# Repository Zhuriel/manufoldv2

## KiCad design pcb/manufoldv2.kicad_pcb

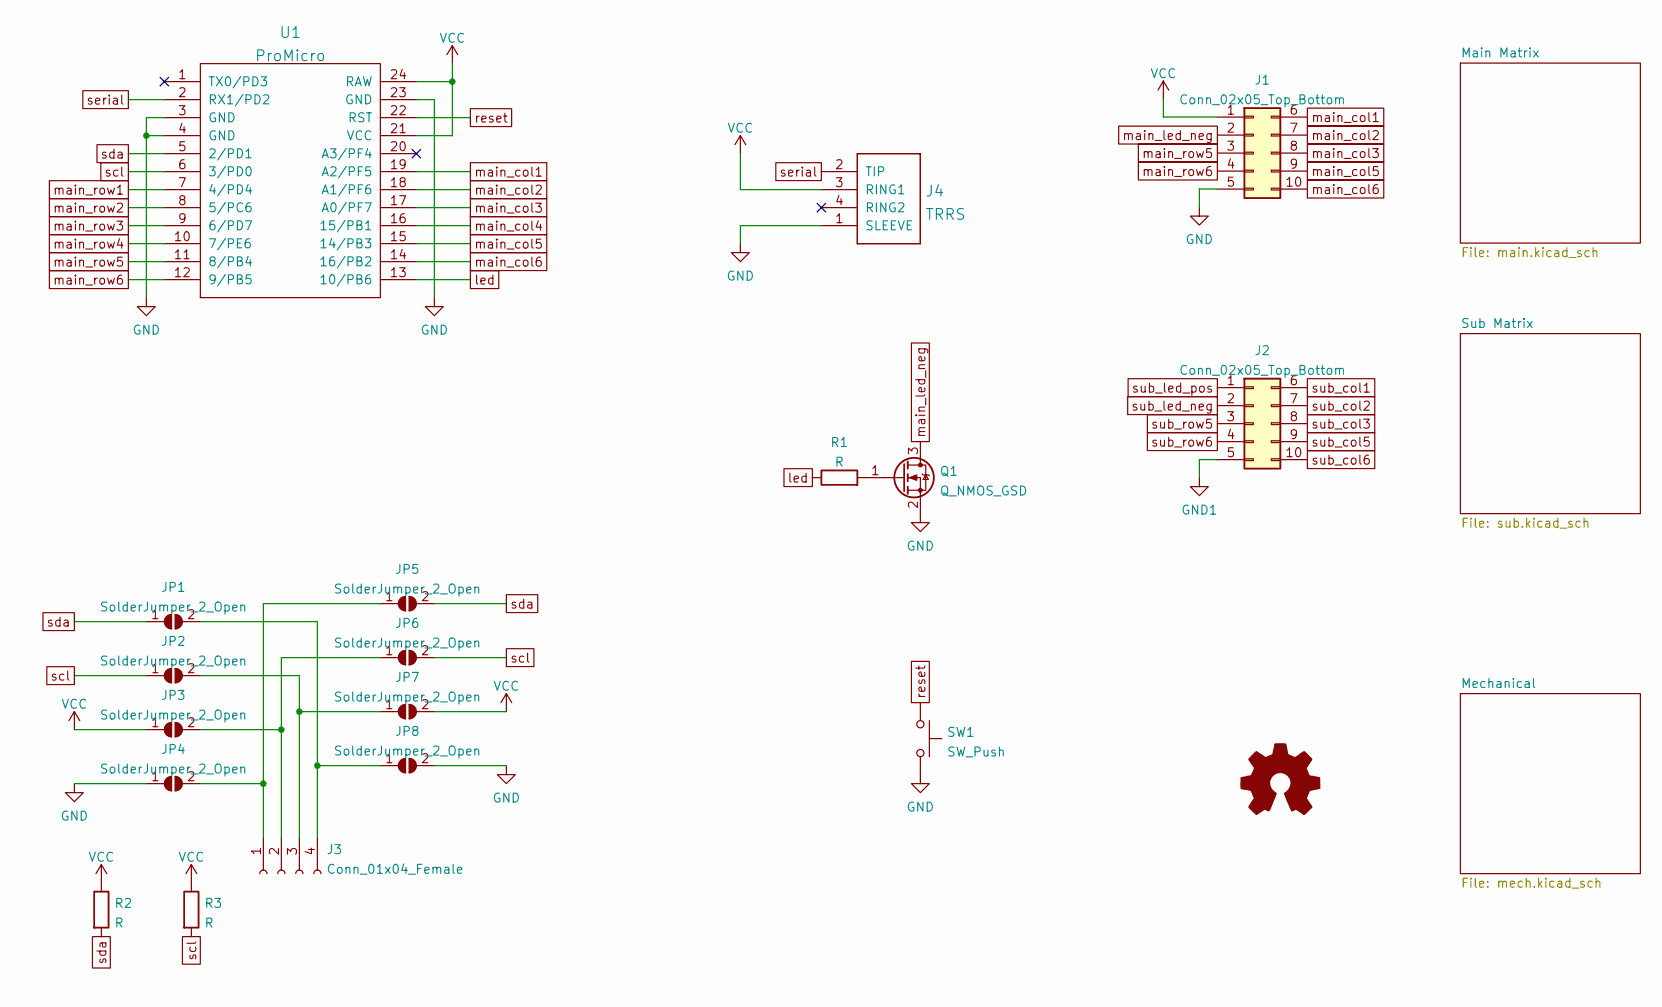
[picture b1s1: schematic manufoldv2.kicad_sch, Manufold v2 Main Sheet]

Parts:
J1: Conn_02x05_Top_Bottom; PinHeader_2x05_P1.27mm_Horizontal
J2: Conn_02x05_Top_Bottom; PinSocket_2x05_P1.27mm_Vertical
J3: Conn_01x04_Female; PinSocket_1x04_P2.54mm_Vertical
J4: TRRS; TRRS-PJ-320A-dual
JP1, JP2, JP3, JP4, JP5, JP6, JP7, JP8: SolderJumper_2_Open; SolderJumper-2_P1.3mm_Open_RoundedPad1.0x1.5mm
Q1: Q_NMOS_GSD; SOT-23_Handsoldering
R1, R2, R3: R; R_0805_2012Metric
SW1: SW_Push; SolderJumper-2_P1.3mm_Open_RoundedPad1.0x1.5mm
U1: ProMicro; promicro_dual

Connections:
GND: J1.5, J4.1 (SLEEVE), JP4.1 (A), JP8.2 (B), Q1.2 (S), SW1.2, U1.3 (GND), U1.4 (GND), U1.23 (GND); also elsewhere on the board
GND1: J2.5; also elsewhere on the board
unnamed: J3.1, JP4.2 (B), JP5.1 (A)
unnamed: J3.2, JP3.2 (B), JP6.1 (A)
unnamed: J3.3, JP2.2 (B), JP7.1 (A)
unnamed: J3.4, JP1.2 (B), JP8.1 (A)
unnamed: Q1.1 (G), R1.2
VCC: J1.1, J4.3 (RING1), JP3.1 (A), JP7.2 (B), R2.1, R3.1, U1.21 (VCC), U1.24 (RAW); also elsewhere on the board
led: R1.1, U1.13 (10/PB6)
main_col1: J1.6, U1.19 (A2/PF5); also elsewhere on the board
main_col2: J1.7, U1.18 (A1/PF6); also elsewhere on the board
main_col3: J1.8, U1.17 (A0/PF7); also elsewhere on the board
main_col4: U1.16 (15/PB1); also elsewhere on the board
main_col5: J1.9, U1.15 (14/PB3); also elsewhere on the board
main_col6: J1.10, U1.14 (16/PB2); also elsewhere on the board
main_led_neg: J1.2, Q1.3 (D); also elsewhere on the board
main_row1: U1.7 (4/PD4); also elsewhere on the board
main_row2: U1.8 (5/PC6); also elsewhere on the board
main_row3: U1.9 (6/PD7); also elsewhere on the board
main_row4: U1.10 (7/PE6); also elsewhere on the board
main_row5: J1.3, U1.11 (8/PB4); also elsewhere on the board
main_row6: J1.4, U1.12 (9/PB5)
reset: SW1.1, U1.22 (RST)
scl: JP2.1 (A), JP6.2 (B), R3.2, U1.6 (3/PD0)
sda: JP1.1 (A), JP5.2 (B), R2.2, U1.5 (2/PD1)
serial: J4.2 (TIP), U1.2 (RX1/PD2)
sub_col1: J2.6; also elsewhere on the board
sub_col2: J2.7; also elsewhere on the board
sub_col3: J2.8; also elsewhere on the board
sub_col5: J2.9; also elsewhere on the board
sub_col6: J2.10; also elsewhere on the board
sub_led_neg: J2.2; also elsewhere on the board
sub_led_pos: J2.1; also elsewhere on the board
sub_row5: J2.3; also elsewhere on the board
sub_row6: J2.4; also elsewhere on the board

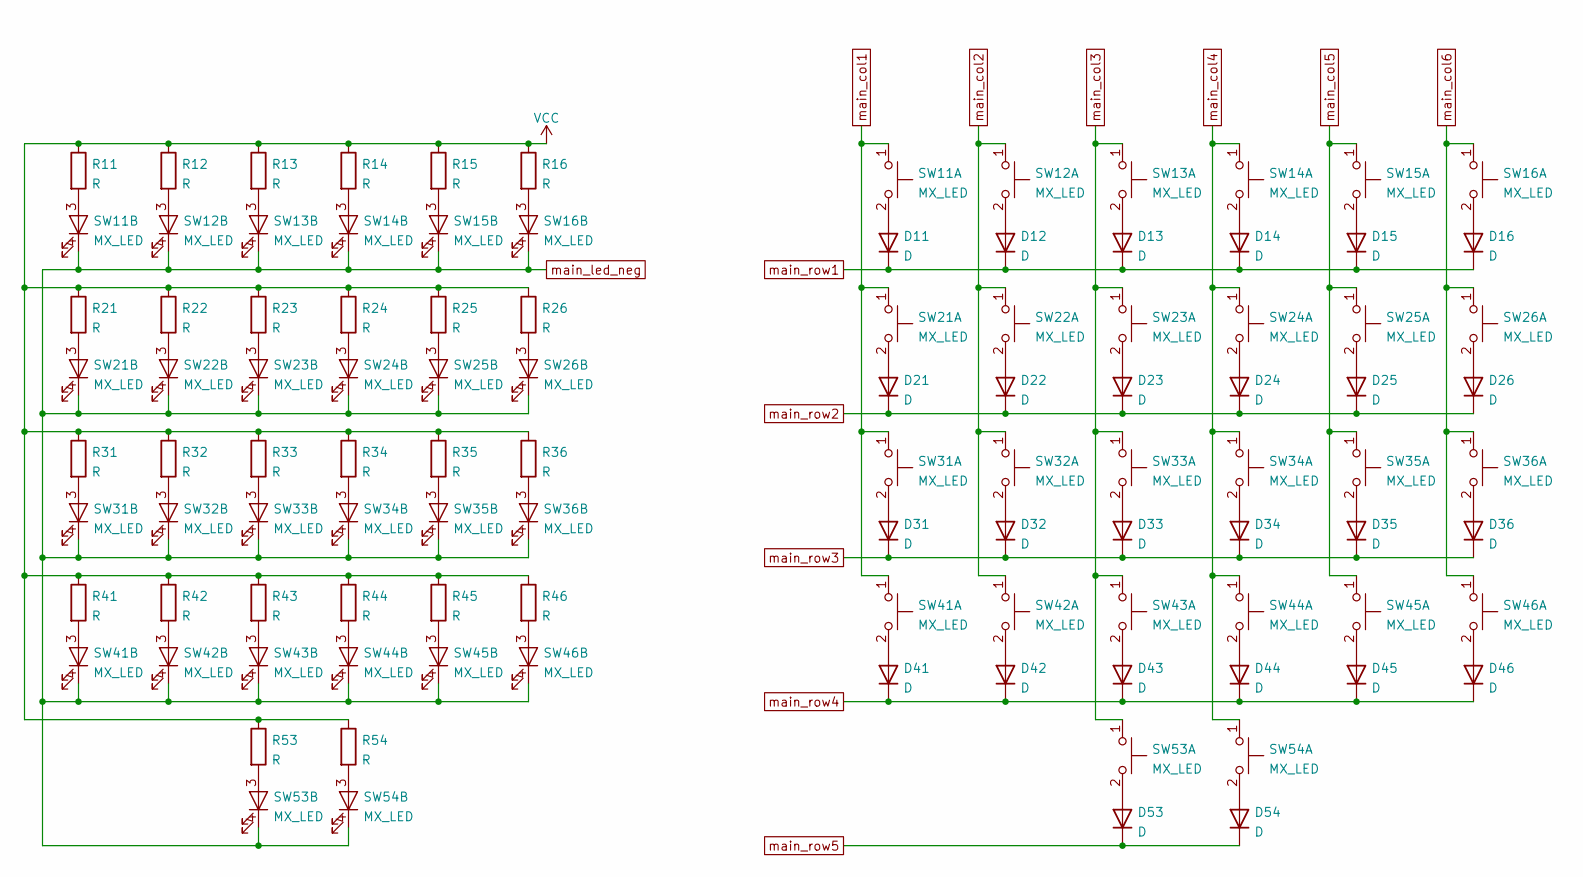
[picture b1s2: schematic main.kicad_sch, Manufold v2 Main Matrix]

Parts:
D11, D12, D13, D14, D15, D16, D21, D22, D23, D24, D25, D26, D31, D32, D33, D34, D35, D36, D41, D42, D43, D44, D45, D46, D53, D54: D; Diode-dual
R11, R12, R13, R14, R15, R16, R21, R22, R23, R24, R25, R26, R31, R32, R33, R34, R35, R36, R41, R42, R43, R44, R45, R46, R53, R54: R; Resistor-Hybrid
SW11, SW12, SW13, SW14, SW15, SW16, SW21, SW22, SW23, SW24, SW25, SW26, SW31, SW32, SW33, SW34, SW35, SW36, SW41, SW42, SW43, SW44, SW45, SW46, SW53, SW54: MX_LED; Triple-Dual-1u-LED

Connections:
unnamed: D11.2 (A), SW11.2
unnamed: D12.2 (A), SW12.2
unnamed: D13.2 (A), SW13.2
unnamed: D14.2 (A), SW14.2
unnamed: D15.2 (A), SW15.2
unnamed: D16.2 (A), SW16.2
unnamed: D21.2 (A), SW21.2
unnamed: D22.2 (A), SW22.2
unnamed: D23.2 (A), SW23.2
unnamed: D24.2 (A), SW24.2
unnamed: D25.2 (A), SW25.2
unnamed: D26.2 (A), SW26.2
unnamed: D31.2 (A), SW31.2
unnamed: D32.2 (A), SW32.2
unnamed: D33.2 (A), SW33.2
unnamed: D34.2 (A), SW34.2
unnamed: D35.2 (A), SW35.2
unnamed: D36.2 (A), SW36.2
unnamed: D41.2 (A), SW41.2
unnamed: D42.2 (A), SW42.2
unnamed: D43.2 (A), SW43.2
unnamed: D44.2 (A), SW44.2
unnamed: D45.2 (A), SW45.2
unnamed: D46.2 (A), SW46.2
unnamed: D53.2 (A), SW53.2
unnamed: D54.2 (A), SW54.2
unnamed: R11.2, SW11.3
unnamed: R12.2, SW12.3
unnamed: R13.2, SW13.3
unnamed: R14.2, SW14.3
unnamed: R15.2, SW15.3
unnamed: R16.2, SW16.3
unnamed: R21.2, SW21.3
unnamed: R22.2, SW22.3
unnamed: R23.2, SW23.3
unnamed: R24.2, SW24.3
unnamed: R25.2, SW25.3
unnamed: R26.2, SW26.3
unnamed: R31.2, SW31.3
unnamed: R32.2, SW32.3
unnamed: R33.2, SW33.3
unnamed: R34.2, SW34.3
unnamed: R35.2, SW35.3
unnamed: R36.2, SW36.3
unnamed: R41.2, SW41.3
unnamed: R42.2, SW42.3
unnamed: R43.2, SW43.3
unnamed: R44.2, SW44.3
unnamed: R45.2, SW45.3
unnamed: R46.2, SW46.3
unnamed: R53.2, SW53.3
unnamed: R54.2, SW54.3
VCC: R11.1, R12.1, R13.1, R14.1, R15.1, R16.1, R21.1, R22.1, R23.1, R24.1, R25.1, R26.1, R31.1, R32.1, R33.1, R34.1, R35.1, R36.1, R41.1, R42.1, R43.1, R44.1, R45.1, R46.1, R53.1, R54.1; also elsewhere on the board
main_col1: SW11.1, SW21.1, SW31.1, SW41.1; also elsewhere on the board
main_col2: SW12.1, SW22.1, SW32.1, SW42.1; also elsewhere on the board
main_col3: SW13.1, SW23.1, SW33.1, SW43.1, SW53.1; also elsewhere on the board
main_col4: SW14.1, SW24.1, SW34.1, SW44.1, SW54.1; also elsewhere on the board
main_col5: SW15.1, SW25.1, SW35.1, SW45.1; also elsewhere on the board
main_col6: SW16.1, SW26.1, SW36.1, SW46.1; also elsewhere on the board
main_led_neg: SW11.4, SW12.4, SW13.4, SW14.4, SW15.4, SW16.4, SW21.4, SW22.4, SW23.4, SW24.4, SW25.4, SW26.4, SW31.4, SW32.4, SW33.4, SW34.4, SW35.4, SW36.4, SW41.4, SW42.4, SW43.4, SW44.4, SW45.4, SW46.4, SW53.4, SW54.4; also elsewhere on the board
main_row1: D11.1 (K), D12.1 (K), D13.1 (K), D14.1 (K), D15.1 (K), D16.1 (K); also elsewhere on the board
main_row2: D21.1 (K), D22.1 (K), D23.1 (K), D24.1 (K), D25.1 (K), D26.1 (K); also elsewhere on the board
main_row3: D31.1 (K), D32.1 (K), D33.1 (K), D34.1 (K), D35.1 (K), D36.1 (K); also elsewhere on the board
main_row4: D41.1 (K), D42.1 (K), D43.1 (K), D44.1 (K), D45.1 (K), D46.1 (K); also elsewhere on the board
main_row5: D53.1 (K), D54.1 (K); also elsewhere on the board

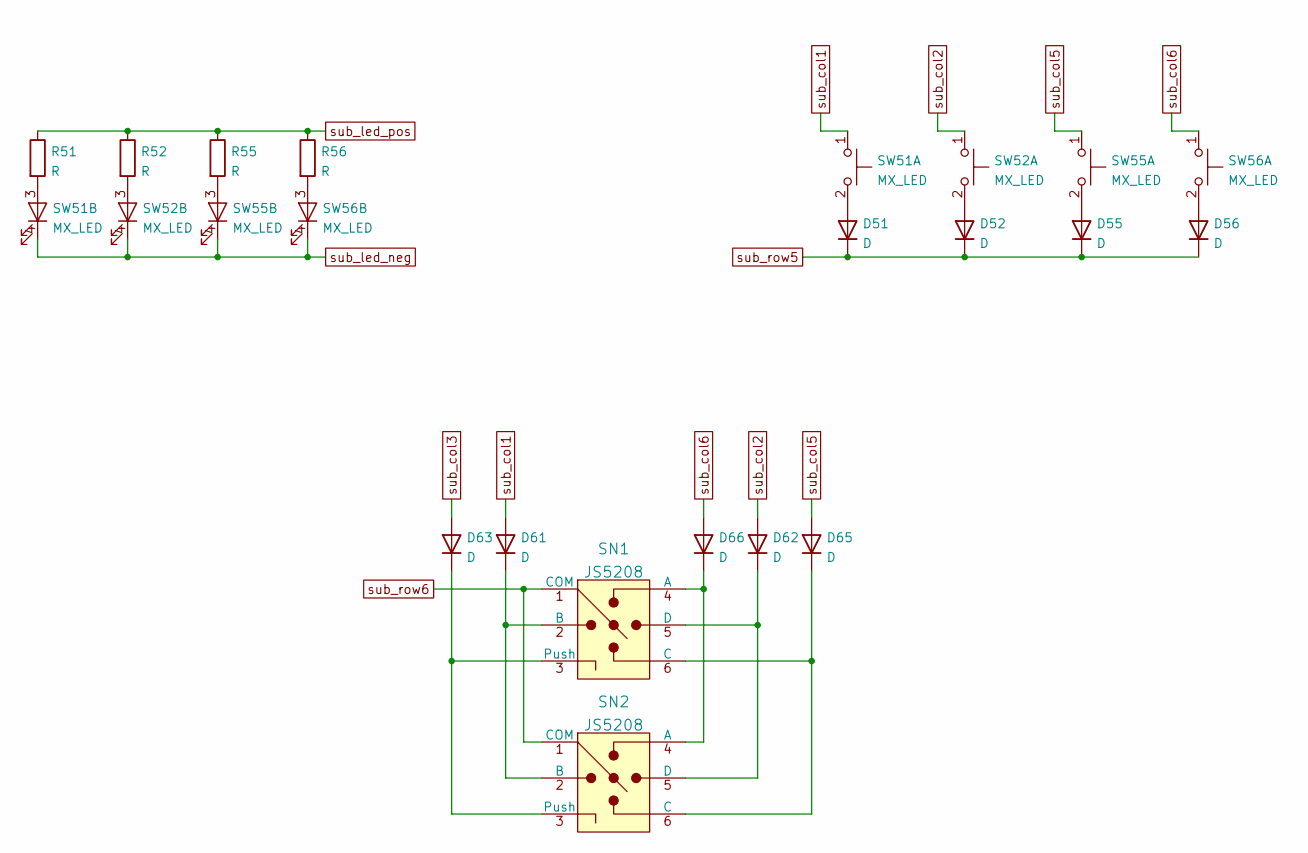
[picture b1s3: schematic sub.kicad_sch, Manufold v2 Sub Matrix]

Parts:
D51, D52, D55, D56: D; Diode-dual
D61, D62, D63, D65, D66: D; D_SOD123F
R51, R52, R55, R56: R; Resistor-Hybrid
SN1, SN2: JS5208; Switch_Nav_12.4x12.4mm_SMD_JS5208; MPN JS5208; Digi-Key_PN EG4561-ND
SW51, SW52, SW55, SW56: MX_LED; Triple-Dual-1u-LED

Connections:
unnamed: D51.2 (A), SW51.2
unnamed: D52.2 (A), SW52.2
unnamed: D55.2 (A), SW55.2
unnamed: D56.2 (A), SW56.2
unnamed: D61.1 (K), SN1.2 (B), SN2.2 (B)
unnamed: D62.1 (K), SN1.5 (D), SN2.5 (D)
unnamed: D63.1 (K), SN1.3 (Push), SN2.3 (Push)
unnamed: D65.1 (K), SN1.6 (C), SN2.6 (C)
unnamed: D66.1 (K), SN1.4 (A), SN2.4 (A)
unnamed: R51.2, SW51.3
unnamed: R52.2, SW52.3
unnamed: R55.2, SW55.3
unnamed: R56.2, SW56.3
sub_col1: D61.2 (A), SW51.1; also elsewhere on the board
sub_col2: D62.2 (A), SW52.1; also elsewhere on the board
sub_col3: D63.2 (A); also elsewhere on the board
sub_col5: D65.2 (A), SW55.1; also elsewhere on the board
sub_col6: D66.2 (A), SW56.1; also elsewhere on the board
sub_led_neg: SW51.4, SW52.4, SW55.4, SW56.4; also elsewhere on the board
sub_led_pos: R51.1, R52.1, R55.1, R56.1; also elsewhere on the board
sub_row5: D51.1 (K), D52.1 (K), D55.1 (K), D56.1 (K); also elsewhere on the board
sub_row6: SN1.1 (COM), SN2.1 (COM); also elsewhere on the board

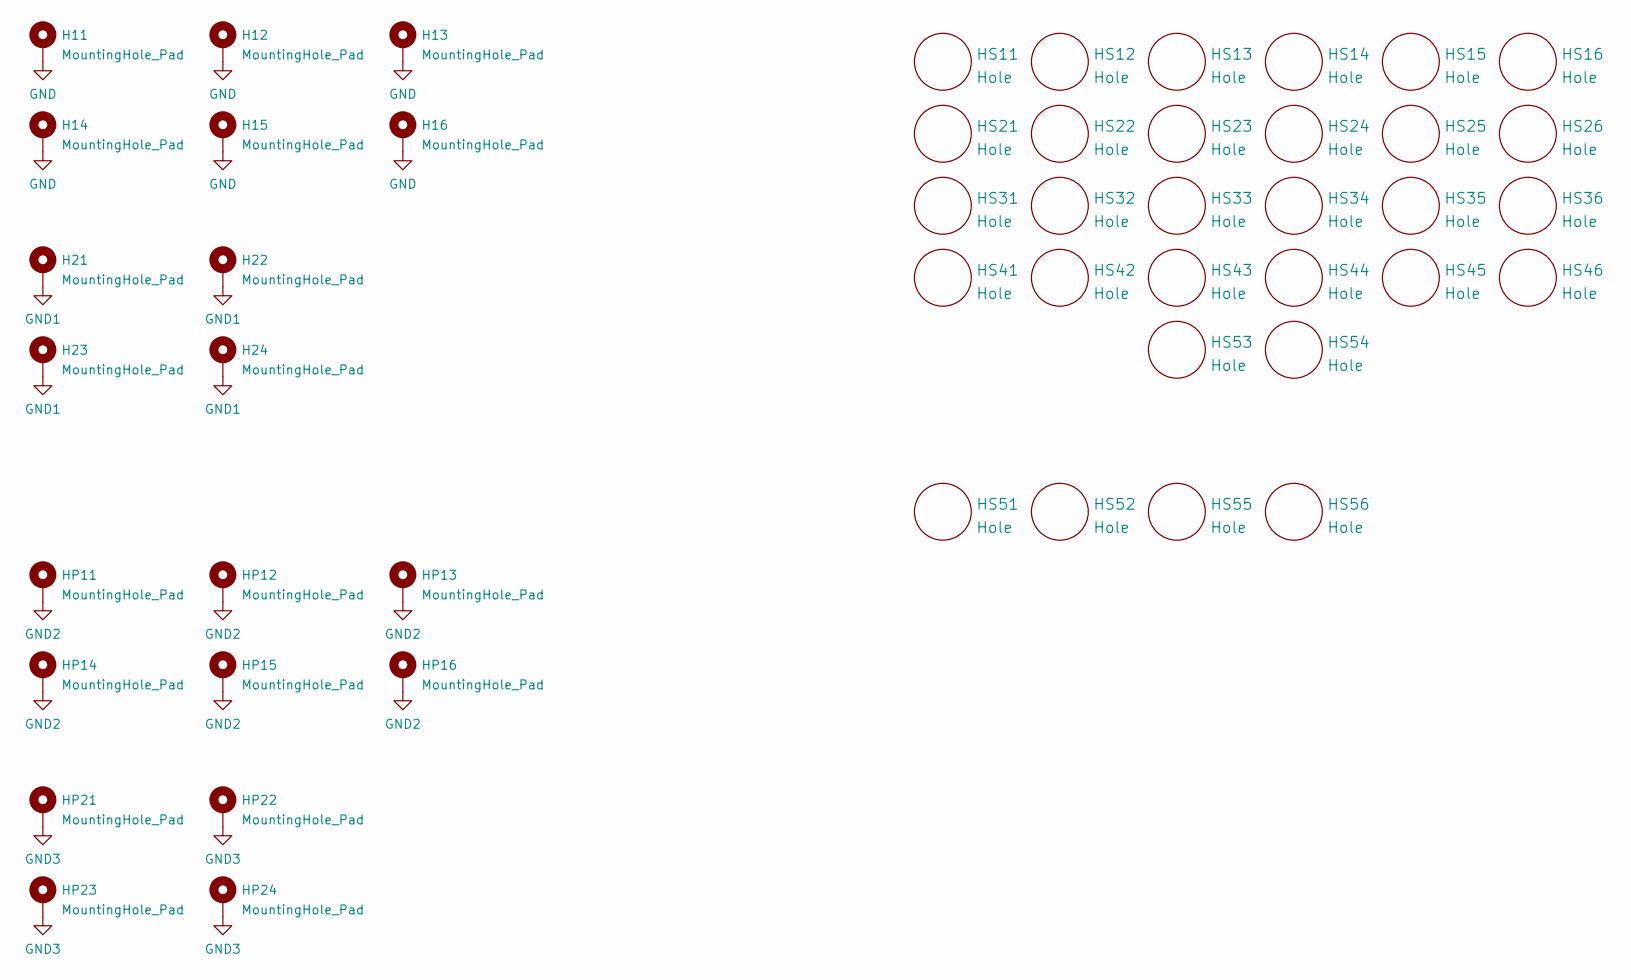
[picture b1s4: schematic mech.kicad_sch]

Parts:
H11, H12, H13, H14, H15, H16, H21, H22, H23, H24: MountingHole_Pad; MountingHole_2.2mm_M2_DIN965_Pad
HP11, HP12, HP13, HP14, HP15, HP16, HP21, HP22, HP23, HP24: MountingHole_Pad; MountingHole_2.2mm_M2_DIN965_Pad
HS11, HS12, HS13, HS14, HS15, HS16, HS21, HS22, HS23, HS24, HS25, HS26, HS31, HS32, HS33, HS34, HS35, HS36, HS41, HS42, HS43, HS44, HS45, HS46, HS51, HS52, HS53, HS54, HS55, HS56: Hole; MX_Switch_Cutout

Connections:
GND: H11.1, H12.1, H13.1, H14.1, H15.1, H16.1; also elsewhere on the board
GND1: H21.1, H22.1, H23.1, H24.1; also elsewhere on the board
GND2: HP11.1, HP12.1, HP13.1, HP14.1, HP15.1, HP16.1
GND3: HP21.1, HP22.1, HP23.1, HP24.1

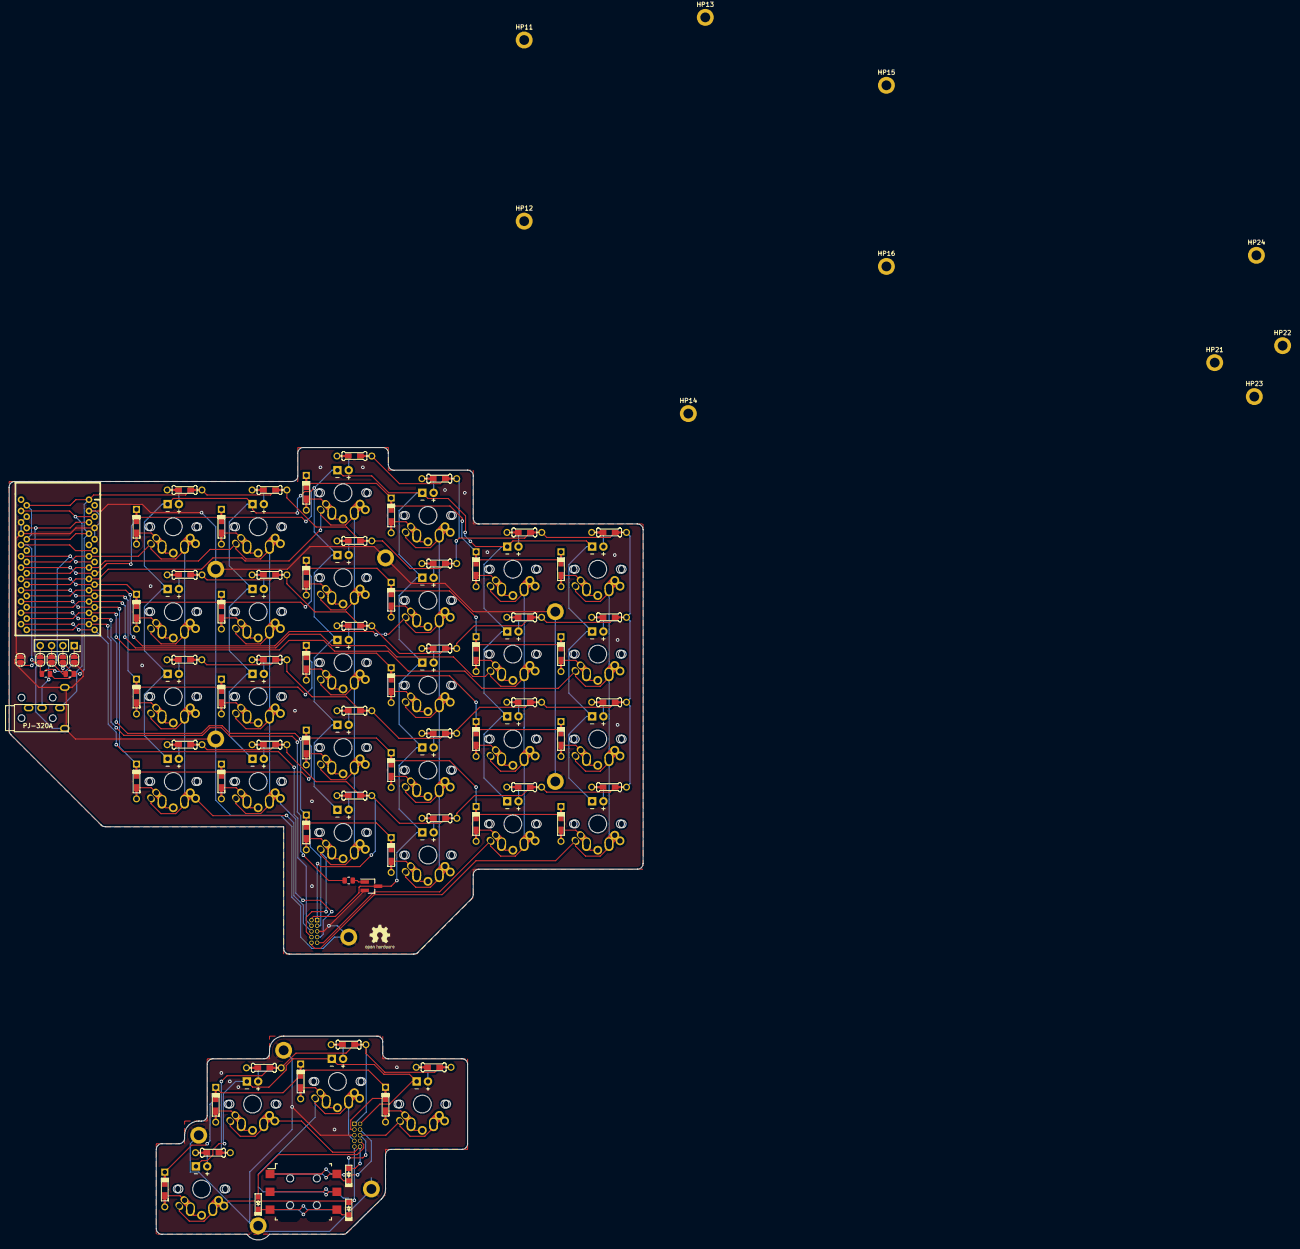
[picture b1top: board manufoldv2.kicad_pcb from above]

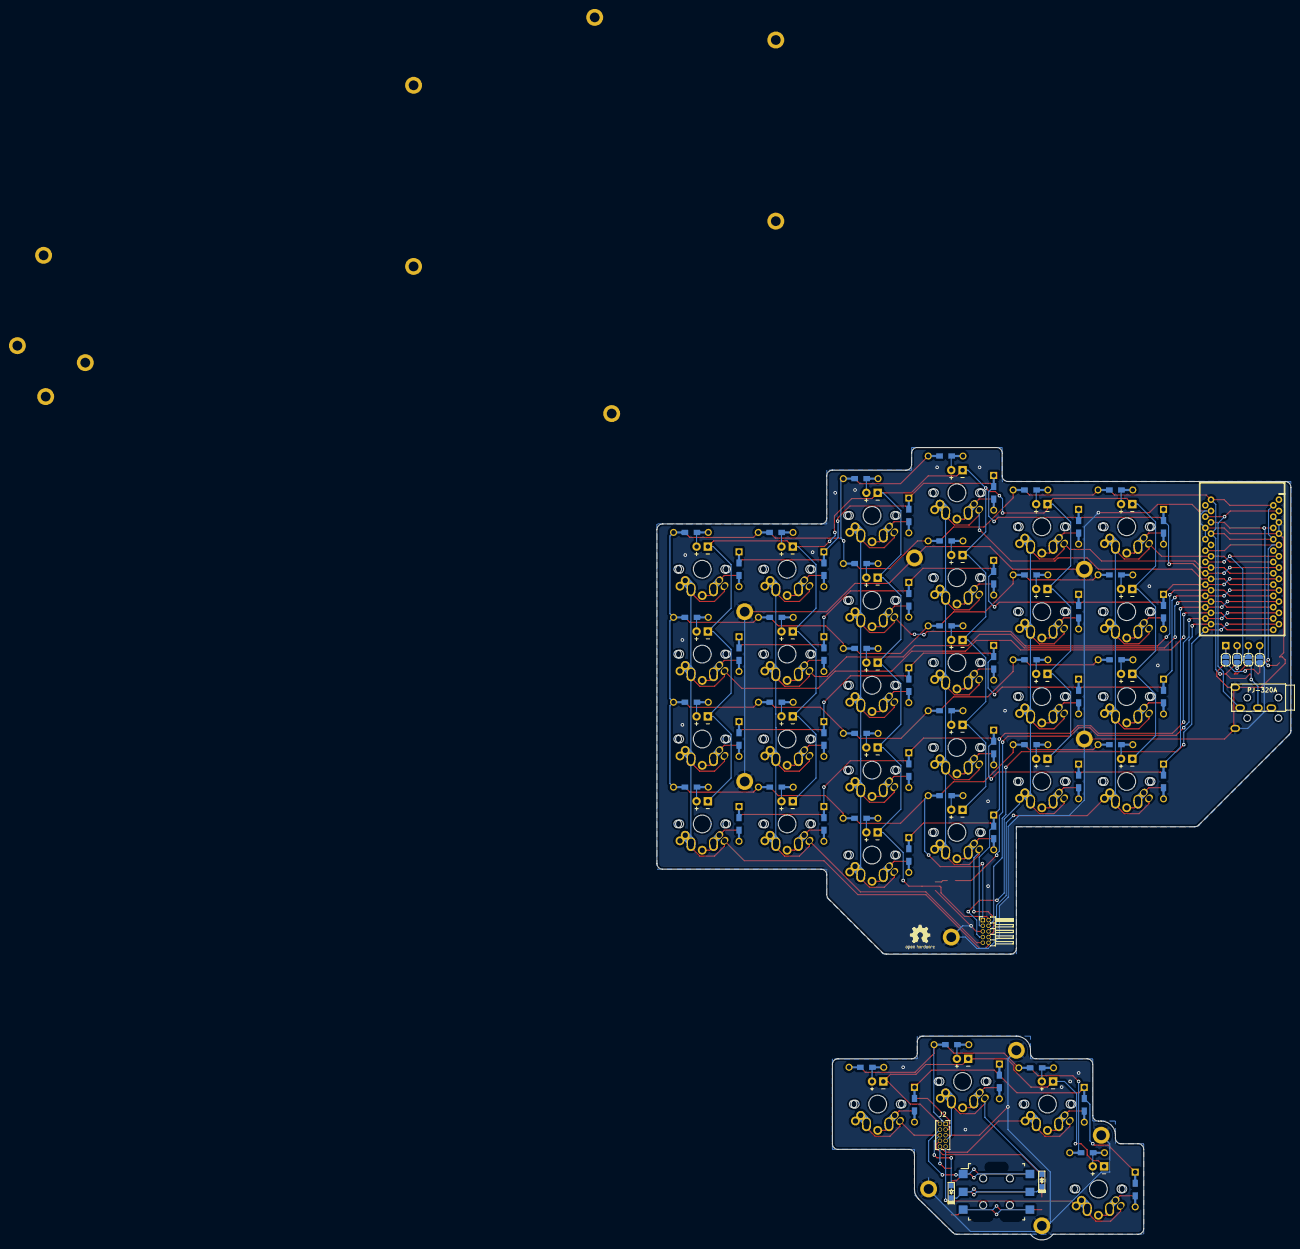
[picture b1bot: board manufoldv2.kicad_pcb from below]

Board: 2 copper layers, 142.2 x 177.8 mm, 165 parts (9 on the bottom side), 102 nets.

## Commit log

2022-01-18 initial kicad project setup
2022-01-18 initial matrix setup
2022-01-19 initial schematic
2022-01-19 add dual promicro footprint, associate footprints
2022-01-23 initial routing
2022-01-23 initial plates
2022-01-24 finish layout and panel
